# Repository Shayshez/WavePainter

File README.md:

# WavePainter
Eurorack conversion kit for Wave2 - Dual channel oscilloscope

[Build guide](WavePainter_Build_Guide.pdf)

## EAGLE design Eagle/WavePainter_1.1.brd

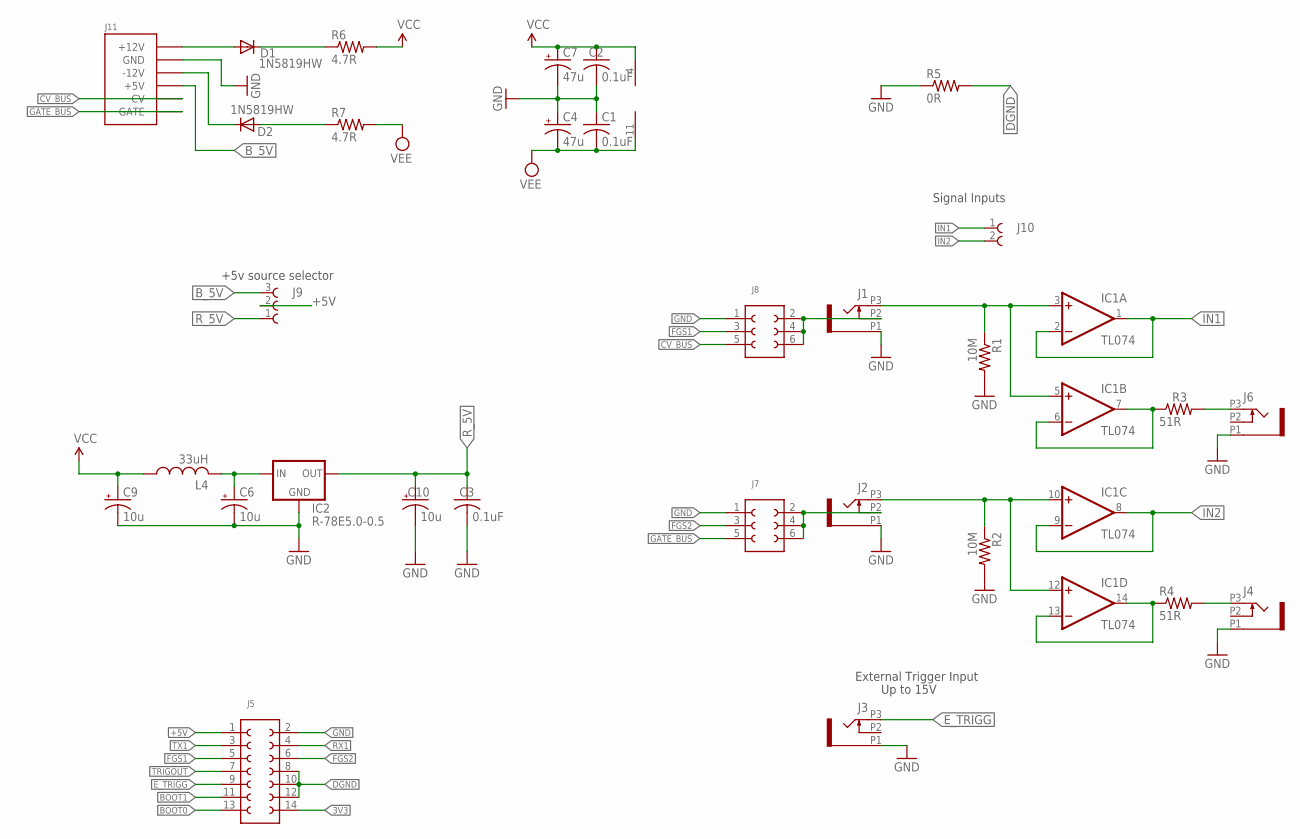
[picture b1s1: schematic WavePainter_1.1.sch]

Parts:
C1, C2, C3: 0.1uF; C0805
C4, C7: 47u; PANASONIC_D
C6, C9, C10: 10u; PANASONIC_B
D1, D2: 1N5819HW; DIODE_SOD123
IC1: TL074; SO14
IC2: R-78E5.0-0.5; SIP3
J1, J2, J3, J4, J6: OG-PJ301_PJ301_THONKICONN7; OG-PJ301_WQP_PJ_301M7
J5: 62001421821
J7, J8: 61300621121
J9: 61300311121
J10: 61300211821
J11: POWER_SHROUDED_NOTEXT; POWER_16_SHROUDED_NOTEXT
L4: 33uH; L3225P
R1, R2: 10M; R0805
R3, R4: 51R; R0805
R5: 0R; R0805
R6, R7: 4.7R; R1206

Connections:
3V3: J5.14 (8)
+5V: J5.1, J9.2
BOOT0: J5.13 (7)
BOOT1: J5.11 (6)
B_5V: J9.3 (1), J11.11 (+5V), J11.12 (+5V)
CV_BUS: J8.5 (3), J11.13 (CV), J11.14 (CV)
DGND: J5.8 (11), J5.10, J5.12 (9), R5.2
E_TRIGG: J3.P3 (3), J5.9 (5)
FGS1: J5.5 (3), J8.3 (2)
FGS2: J5.6 (12), J7.3 (2)
GATE_BUS: J7.5 (3), J11.15 (GATE), J11.16 (GATE)
GND: C1.1, C2.2, C3.2, C4.+, C6.-, C7.-, C9.-, C10.-, IC2.2 (GND), J1.P1 (1), J2.P1 (1), J3.P1 (1), J4.P1 (1), J5.2 (14), J6.P1 (1), J7.1, J8.1, J11.3 (GND), J11.4 (GND), J11.5 (GND), J11.6 (GND), J11.7 (GND), J11.8 (GND), R1.2, R2.2, R5.1
IN1: IC1.1 (OUT), IC1.2 (-IN), J10.1
IN2: IC1.8 (OUT), IC1.9 (-IN), J10.2
unnamed: IC1.10 (+IN), IC1.12 (+IN), J2.P3 (3), R2.1
unnamed: D2.C, J11.1 (-12V), J11.2 (-12V)
unnamed: C6.+, IC2.1 (IN), L4.2
unnamed: D1.A, J11.9 (+12V), J11.10 (+12V)
unnamed: IC1.3 (+IN), IC1.5 (+IN), J1.P3 (3), R1.1
unnamed: J4.P3 (3), R4.2
unnamed: D1.C, R6.1
unnamed: D2.A, R7.1
unnamed: J6.P3 (3), R3.2
unnamed: IC1.6 (-IN), IC1.7 (OUT), R3.1
unnamed: IC1.13 (-IN), IC1.14 (OUT), R4.1
unnamed: J1.P2 (2), J8.2 (6), J8.4 (5), J8.6 (4)
unnamed: J2.P2 (2), J7.2 (6), J7.4 (5), J7.6 (4)
RX1: J5.4 (13)
R_5V: C3.1, C10.+, IC2.3 (OUT), J9.1 (3)
TRIGOUT: J5.7 (4)
TX1: J5.3 (2)
VCC: C2.1, C7.+, C9.+, IC1.4 (V+), L4.1, R6.2
VEE: C1.2, C4.-, IC1.11 (V-), R7.2

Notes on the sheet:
Signal Inputs
+5v source selector
External Trigger Input
Up to 15V

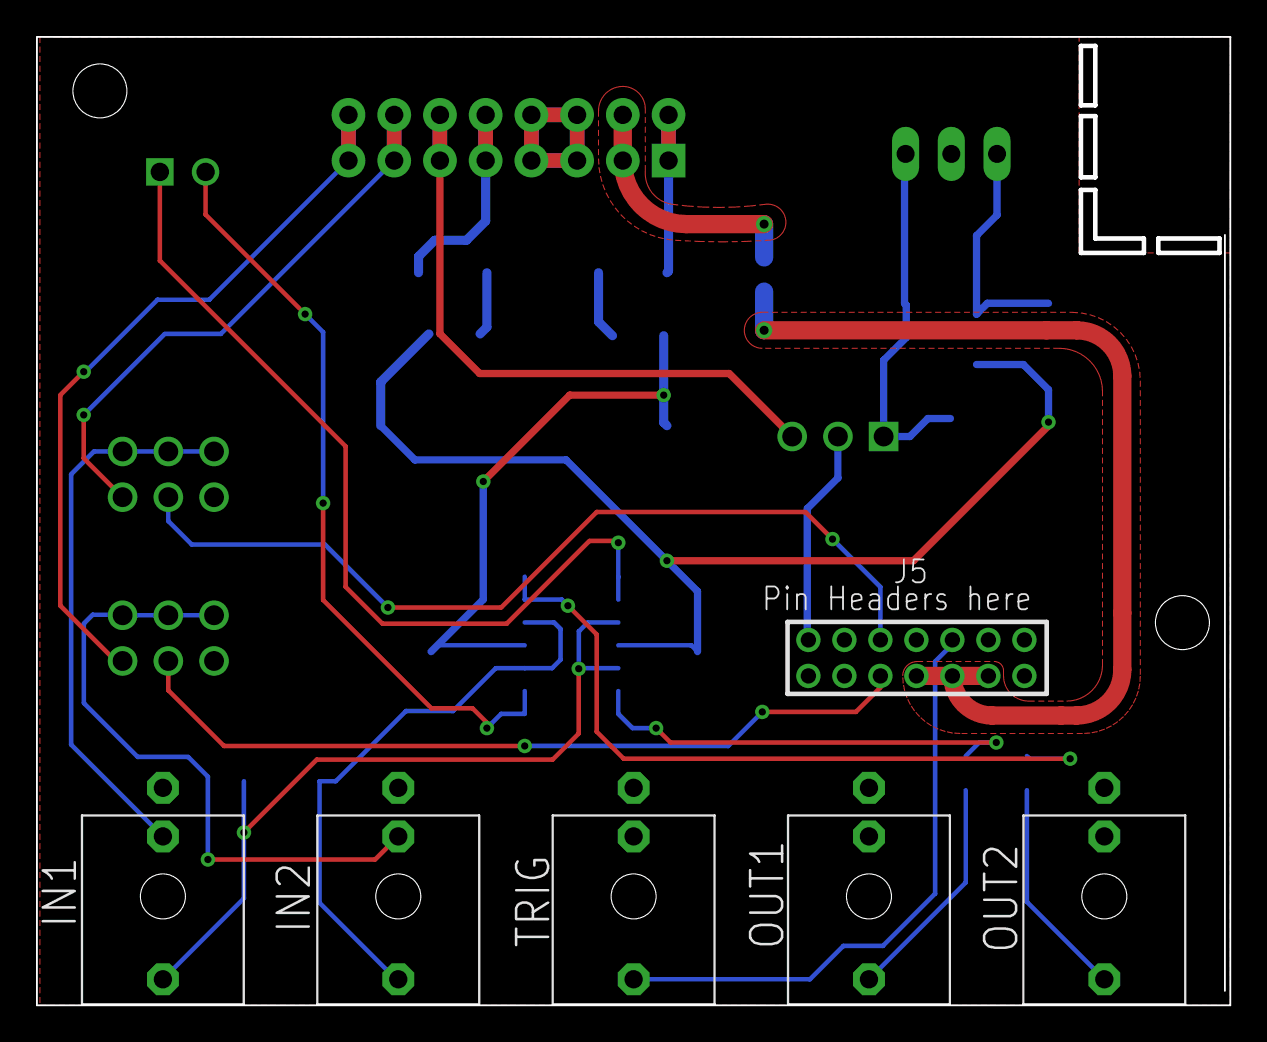
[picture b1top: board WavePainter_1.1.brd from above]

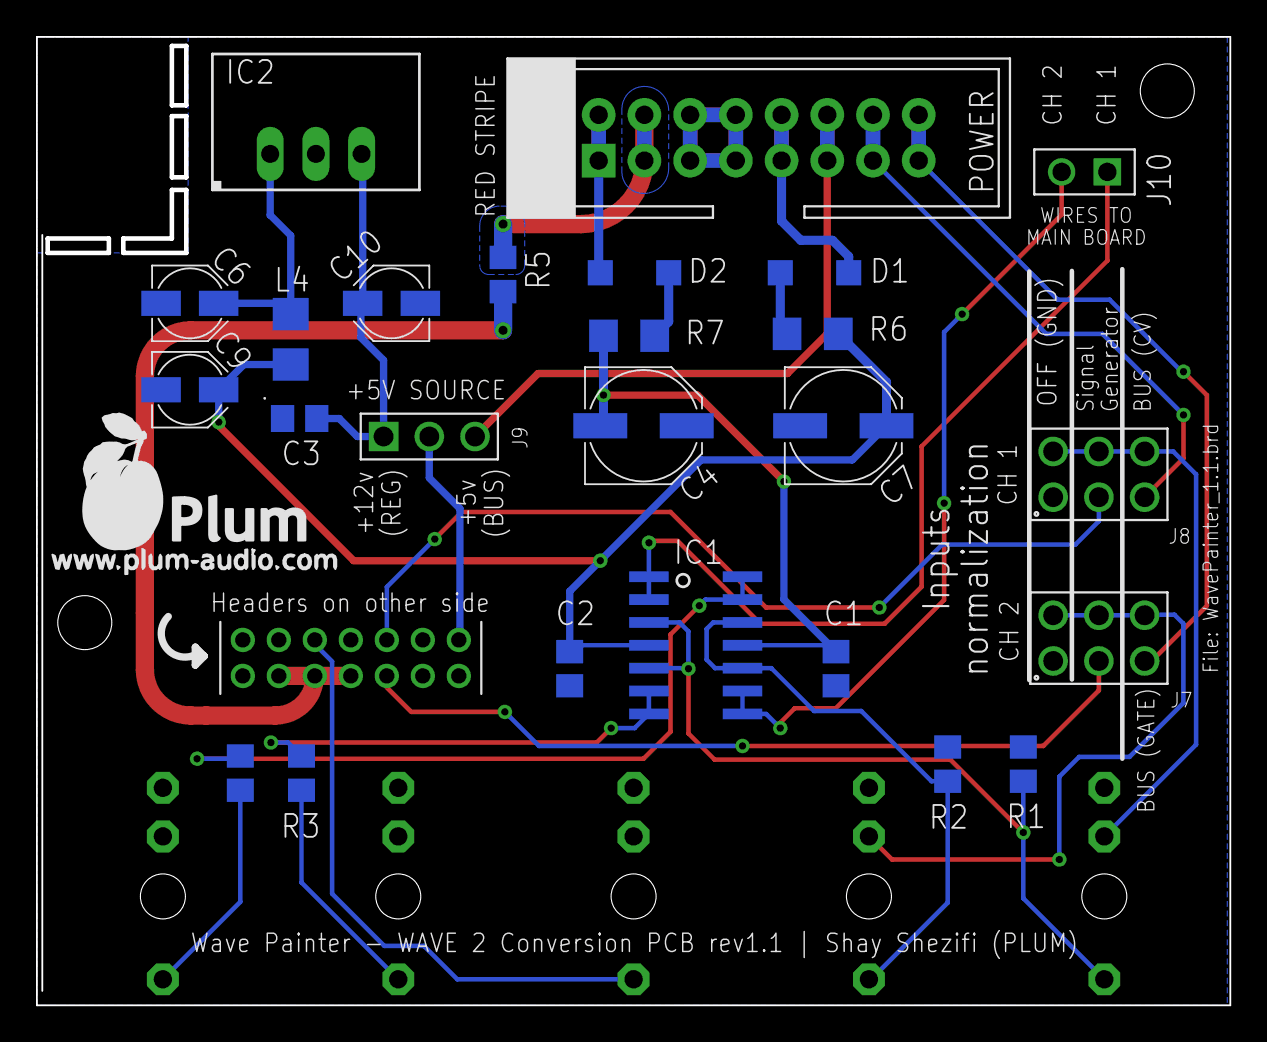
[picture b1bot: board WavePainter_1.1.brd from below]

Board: 2 copper layers, 66.1 x 53.6 mm, 31 parts (26 on the bottom side), 27 nets.

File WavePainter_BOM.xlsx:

Qty | Value | Device | Package | Parts | Mouser ref | Description
1 |  | WAVE2 Partial kit from Pusherman or DIY kit from JYETEC
1 |  | WavePainter conversion PCB from Pusherman
1 |  | WavePainter Panel from Pusherman
 | Resistors
1 | 0R | R-US_R0805 | R0805 | R5 | 603-RC0805FR-130RL | RESISTOR, American symbol
2 | 4.7R | R-US_R1206 | R1206 | R6, R7 | 603-RC1206FR-074R7L | RESISTOR, American symbol
2 | 51R | R-US_R0805 | R0805 | R3, R4 | 603-RC0805JR-7W51RL | RESISTOR, American symbol
2 | 10M | R-US_R0805 | R0805 | R1, R2 | 603-RC0805FR-0710ML | RESISTOR, American symbol
 | Caps
3 | 0.1uF | C-USC0805 | C0805 | C1, C2, C3 | 80-C0805C104J5RAUTO | CAPACITOR, American symbol
3 | 10u | CPOL-USC | PANASONIC_B | C6, C9, C10 | 667-EEE-FK1E100R | POLARIZED CAPACITOR, American symbol
2 | 47u | CPOL-USD | PANASONIC_D | C4, C7 | 667-EEE-1EA100SR | POLARIZED CAPACITOR, American symbol
 | Inductor
1 | 33uH | L-USL3225P | L3225P | L4 | 963-LB3218T330K | INDUCTOR, American symbol
 | Chips
2 | 1N5819HW | DIODE_DIODE-SOD123 | DIODE_SOD123 | D1, D2 | 621-1N5819HW-F | DIODE
1 | R-78E5.0-0.5 | R-78E5.0-0.5 | SIP3 | IC2 | 919-R-78E5.0-0.5 | Innoline R-78xx-0.5 Series Switching Regulators - 0.5A, Low Cost
1 | TL074 | TL074D | SO14 | IC1 | 595-TL074CDR | OP AMP
 | Misc
1 | Pin Headers Male 2.54 - 2pins | PINHEAD 2.54mm 2p |  | J10 | 855-M20-9774046 | Pin Headers 2.54mm - row of 40pins - cut 2 for J10 and 3 for J9
1 | Pin Headers Male 2.54 - 3pins | PINHEAD 2.54mm 3p |  | J9
2 | Pin Headers Male 2.54 - 2X3pins | PINHEAD 2.54mm Dual row of 3p |  | J7, J8 | 649-77313-124-40LF | Pin Headers 2.54mm - dual row of 40pins - cut for J7/J8
1 | Pin Headers male 2.00mm 14 pins (2X7) | Pin Headers 2.00mm |  | J5 | 855-M22-2020705 | WR-PHD 2.00mm Dual Socket Header, 14 Pins=>Code : Con_BTB_SHD_2.00_2_62001421821
3 | Mini Jumper Cover |  |  |  | 855-M7582-05
2 | Jumper Wire 10cm |  |  |  | 854-ZW-FF-10 | Pack of 40 - only 2 needed
3 | Black Screw M3 / > 10mm Length |  |  |  | https://www.aliexpress.com/item/32965979997.html | To attach the panel
1 | Standoff Spacer M3 / 8mm Length |  |  |  | https://www.aliexpress.com/item/32800873842.html | Nylon is better
2 | Standoff Spacer M3 / 5mm Length |  |  |  | https://www.aliexpress.com/item/32800873842.html | Nylon is better
5 | PJ398SM_THONKICONN | PJ398SM_THONKICONN | WQP_PJ398SM | J1, J2, J3, J4, J6 | https://www.thonk.co.uk/shop/thonkiconn/
1 | Power Header 16 pins | POWER_SHROUDED | POWER_16_SHROUDED | J11 | 538-70246-1604
 | For scope bards
1 | Pin Headers female 2.00mm 14 pins (2X7) | Pin Headers socket 2.00mm | for scope main board | J5 | 855-M22-7140742 | WR-PHD 2.00mm Dual Socket Header, 14 Pins=>Code : Con_BTB_SHD_2.00_2_62001421821
1 | PEC11 Encoder | PEC11L-4220F-S0015 | 15PPR / 30 DETENT / SLIM | SW5 | 652-PEC11L4220FS0015 (20mm shaft) or 652-PEC11L4215FS0015 (15mm shaft)
1 | Knob D Shaft for the encoder | Sifam D-shaft 12mm |  |  | https://www.thonk.co.uk/shop/sifam-soft-touch-encoder-knobs/

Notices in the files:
parts and their libraries:
Wurth_Elektronik_Electromechanic_Board_t: Copyright: Würth Elektronik
r-78xx_10: (c) 2015 Samuel Lourenço
